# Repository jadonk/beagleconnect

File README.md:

# BeagleConnect
The purpose of BeagleConnect is to eliminate the need to write software to connect to a massive library of [sensors](https://en.wikipedia.org/wiki/Sensor), [actuators](https://en.wikipedia.org/wiki/Actuator) and [indicators](https://en.wikipedia.org/wiki/Indicator_(distance_amplifying_instrument)). These are the tools used to automate things in [mechatronics](https://en.wikipedia.org/wiki/Mechatronics) and [IoT](https://en.wikipedia.org/wiki/Internet_of_things).

BeagleConnect solves:
* The need to write software to add a large set of diverse devices to your system,
* The need to maintain the software with security updates,
* The need to rapidly prototype using off-the-shelf software and hardware without wiring,
* The need to connect to devices using long-range, low-power wireless, and
* The need to produce high-volume custom hardware cost-optimized for your requirements.

The minimally viable BeagleConnect development release:
* Supports at least 100 mikroBUS-based Click boards from Mikroelectronika,
* Works with BLE-enabled Linux computers at 2.4GHz,
* Works on long-range sub-GHz at 500m with data rates of 1kbps, and
* Comprises of low-cost BeagleBoard.org Linux SBC, a BeagleConnect gateway, and at least 10 BeagleConnect device nodes each supporting 2 add-on devices.

A wireless BeagleConnect board for adding a new device node is targeted to cost under US$10.

Future releases will be collaborated with the community, evolve dynamically, and contain additional functionality. The goal is to support over 500 add-on devices within the first year after the development release.

_Aside_: The term BeagleConnect refers to a particular board as well as a family of boards, a collection of Linux kernel drivers, microcontroller firmware, communication protocol, and system-level integration to automation software tools. More specific terms will be applied in the architecture details. The term is meant to represent the experience to be introduced to users through the initial BeagleConnect board.

## BeagleConnect wireless board prototype rev B

# What is new?
BeagleConnect solves IoT in a different and better way than any previous solution.

## The device interface software is already done
BeagleConnect uses the collaboratively developed Linux kernel to contain the intelligence required to speak to these devices (sensors, actuators, and indicators), rather than relying on writing code on a microcontroller specific to these devices. Some existing solutions rely on large libraries of microcontroller code, but the integration of communications, maintenance of the library with a limited set of developer resources and other constraints to be explained later make those other solutions less suitable for rapid prototyping than BeagleConnect.

Linux presents these devices abstractly in ways that are self-descriptive. Add an accelerometer to the system and you are automatically fed a stream of force values in standard units. Add a temperature sensor and you get it back in standard units again. Same for sensing magnetism, proximity, color, light, frequency, orientation, or multitudes of other inputs. Indicators, such as LEDs and displays, are similarly abstracted with a few other kernel subsystems and more advanced actuators with and without feedback control are in the process of being developed and standardized. In places where proper Linux kernel drivers exist, no new specialized code needs to be created for the devices.

*Bottom line*: For hundreds of devices, users won't have to write a single line of code to add them their systems. The automation code they do write can be extremely simple, done with graphical tools or in any language they want. Maintenance of the code is centralized in a small reusable set of microcontroller firmware and the Linux kernel, which is highly peer reviewed under a [highly-regarded governance model](https://wiki.p2pfoundation.net/Linux_-_Governance).

## On-going maintenance
Because there isn't code specific to any given network-of-devices configuration, we can all leverage the same software code base. This means that when someone fixes an issue in either BeagleConnect firmware or the Linux kernel, you benefit from the fixes. The source for BeagleConnect firmware is also submitted to the [Zephyr Project](https://www.zephyrproject.org/) upstream, further increasing the user base. Additionally, we will maintain stable branches of the software and provide mechanisms for updating firmware on BeagleConnect hardware. With a single, relatively small firmware load, the potential for bugs is kept low. With large user base, the potential for discovering and resolving bugs is high.

## Rapid prototyping without wiring
BeagleConnect utilizes the [mikroBUS standard](https://elinux.org/Mikrobus). The mikroBUS standard interface is flexible enough for almost any typical sensor or indicator with hundreds of devices available.

## Long-range, low-power wireless
BeagleConnect wireless hardware is built around a [TI CC1352](http://www.ti.com/product/CC1352R) with TODO benefits.

## Full customization possible
BeagleConnect utilizes [open source hardware](https://www.oshwa.org/definition/) and [open source software](https://en.wikipedia.org/wiki/Open-source_software), making it possible to optimize hardware and software implementations and sourcing to meet end-product requirements. BeagleConnect is meant to enable rapid-prototyping and not to necessarily satisfy any particular end-product's requirements, but with full considerations for go-to-market needs.

BeagleConnect is:
* Available for at least 10 years,
* Built with fully open source software with submissions to mainline Linux and Zephyr repositories to aide in support and porting,
* Built with fully open source and non-restrictive hardware design including schematic, bill-of-materials, layout, and manufacturing files (with only the BeagleBoard.org logo removed due to licensing restrictions of our brand),
* Built with parts where at least a compatible part is available from worldwide distributors in any quantity,
* Built with design and manufacturing partners able to help scale derivative designs,
* Based on a security model using public/private keypairs that can be replaced to secure your own network, and
* Fully FCC/CE certified.

# Usage and development

## BeagleConnect user experience

### Enable a Linux host with BeagleConnect

Log into a host system running Linux that is BeagleConnect enabled. Enable a Linux host with BeagleConnect by plugging a BeagleConnect board into it's USB port. You'll also want to have another BeagleConnect board with a sensor, actuator or indicator device on it.

TODO: Currently the host is shown to be a PocketBeagle with a cape, but should likely be a different SBC with a BeagleConnect board connected over USB.

TODO: Currently the device is shown to be a Sensortag, but should likely be shown as a BeagleConnect with a Click Board device on it and a battery.

### Connect host and device

Initiate a connection between the host and devices by pressing the discovery button(s).

### Device data shows up as files

New streams of self-describing data show up on the host system using native device drivers.

## Components
* Host-side: BeagleConnect board connects a CC1352 to a Beagle or other Linux host over USB to serial
   * Provides long-range, low-power wireless communications
* Device-side: BeagleConnect board with a CC1352 is powered by a battery (coin cell or JST connector) or USB connector
   * Provides 2 mikroBUS connectors for connecting any of hundreds of [Click Board](https://bbb.io/click) mikroBUS add-on devices
* Standard firmware on the host-side and target-side CC1352s transport the standard busses
   * Paired with a Linux kernel driver
   * Provides new Linux host controllers for SPI, I2C, UART, PWM, ADC, and GPIO with interrupts
* Two-step provisioning
   * Enter provisioning mode by pressing the button on the host-side BeagleConnect
   * Press the button on any powered device-side BeagleConnect to add it to the network
      * The device interfaces get exposed to the host via Greybus BRIDGED_PHY protocol
      * The I2C bus is probed for a an identifier EEPROM and appropriate device drivers are loaded on the host
      * Unsupported Click Boards connected are exposed via userspace drivers on the host for development

### What's different
* No microcontroller code development is required by users
* Userspace drivers make rapid prototyping really easy
* Kernel drivers makes the support code collaborative parts of the Linux kernel, rather than cut-and-paste

## Development platform
* Linux machine
* 2x [CC1352R Launchpad](http://www.ti.com/tool/launchxl-cc1352r1)
* [Click BoosterPack 2](https://www.mikroe.com/click-booster-pack-2)

# Technical approach

BeagleConnect uses Greybus and updated Click Boards with identifiers to eliminate the need to add manually configure devices added onto the Linux system.

## High-level
* For Linux nerds: Think of BeagleConnect as [6LoWPAN](https://en.wikipedia.org/wiki/6LoWPAN) over [802.15.4](https://en.wikipedia.org/wiki/IEEE_802.15.4)-based [Greybus](https://kernel-recipes.org/en/2015/talks/an-introduction-to-greybus/) (instead of Unipro as used by Project Ara), where every BeagleConnect board shows up as new SPI, I2C, UART, PWM, ADC, and GPIO controllers that can now be probed to load drivers for the sensors or whatever is connected to them. (Proof of concept of Greybus over TCP/IP: https://www.youtube.com/watch?v=7H50pv-4YXw)
* For MCU folks: Think of BeagleConnect as a [Firmata](https://github.com/firmata/protocol)-style firmware load that exposes the interfaces for remote access over a secured wireless network. However, instead of using host software that knows how to speak the Firmata protocol, the Linux kernel speaks the slightly similar Greybus protocol to the MCU and exposes the device generically to users using a Linux kernel driver. Further, the Greybus protocol is spoken over [6LoWPAN](https://en.wikipedia.org/wiki/6LoWPAN) on [802.15.4](https://en.wikipedia.org/wiki/IEEE_802.15.4).

## Software architecture
* 802.15.4 provides the 

## TODO items
* Linux kernel driver
* Provisioning
   * Kconfig and what-not for adding a new BeagleDust to the network
   * Kconfig and what-not for configuring Clicks connected to BeagleDust
* Firmware for host CC13x
* Firmware for device CC13x
* Click Board drivers and device tree formatted metadata for 100 or so Click Boards
* Click Board plug-ins for node-red for the same 100 or so Click Boards
* BeagleDust System Reference Manual and FAQs

## Associated pre-work
* Click Board support for Node-RED can be executed with native connections on PocketBeagle+TechLab and BeagleBone Black with mikroBUS Cape
   * Device tree fragments and driver updates can be provided via https://bbb.io/click
* The Kconfig style provisioning can be implemented for those solutions, which will require a reboot. We need to centralize edits to /boot/uEnv.txt to be programmatic. As I think through this, I don't think BeagleConnect is impacted, because the Greybus-style discovery along with Click EEPROMS will eliminate any need to edit /boot/uEnv.txt.

## User experience concerns
* Make sure no reboots are required
* Plugging BeagleConnect into host should trigger host configuration
* Click EEPROMs should trigger loading whatever drivers are needed and provisioning should load any new drivers
* Userspace (spidev, etc.) drivers should unload cleanly when 2nd phase provisioning is completed

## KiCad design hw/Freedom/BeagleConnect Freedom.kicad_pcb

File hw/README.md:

# BeagleConnect HW

The LeashPCB is a newer chip based version of BeagleConnect Long-range Wireless BLE(2.4GHz)/802.15.4(SubG), started in June of 2019

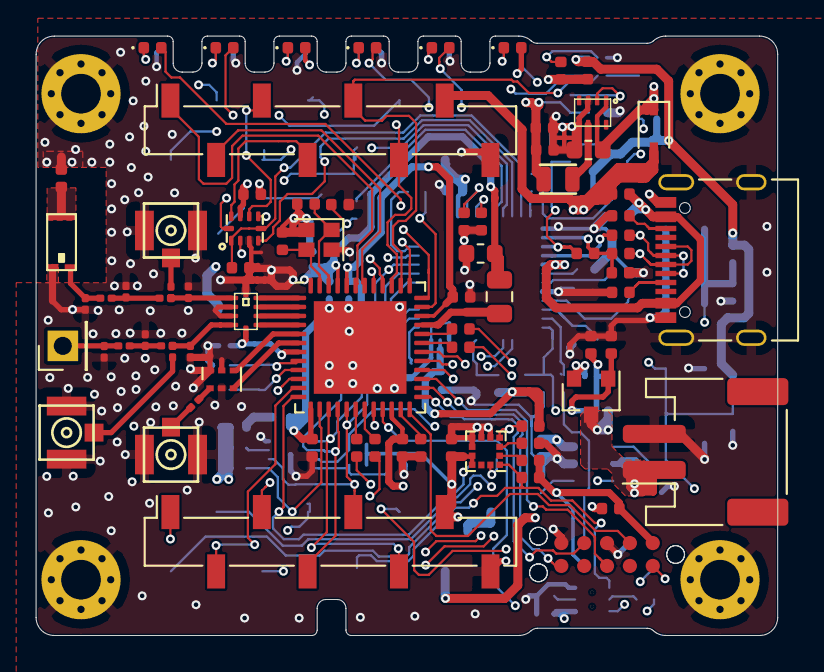
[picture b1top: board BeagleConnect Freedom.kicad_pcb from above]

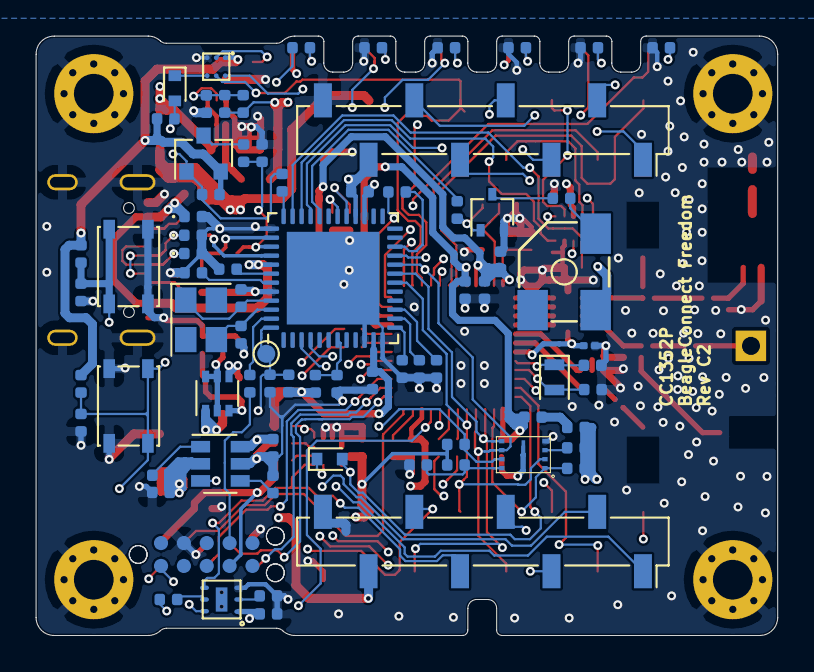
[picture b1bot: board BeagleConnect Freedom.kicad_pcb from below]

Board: 4 copper layers, 41.2 x 33.3 mm, 156 parts (76 on the bottom side), 122 nets.

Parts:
AE1: Antenna_Dipole; RFECA3216060A1T
AE2: Antenna; PinHeader_1x01_P2.54mm_Vertical
B1: 0900PC15A0036E; 0900PC15A0036
B2: 1720BL15B0200E; Anaren_0805_2012Metric-6
BZ1: Buzzer; BUZZER3-5.5X5X2MM
C1, C5, C7, C18, C19, C20, C21, C22, C23, C25, C26, C38, C39, C40, C41, C42: 0.1U; C_0402_1005Metric
C2: 1N; C_0402_1005Metric
C3, C4: 18P; C_0402_1005Metric
C6, C10, C11, C14, C45: 10U; C_0402_1005Metric
C8, C44: 220N; C_0402_1005Metric
C9: 0.47U; C_0402_1005Metric
C12: 10U; C_0603_1608Metric
C13: 100P; C_0402_1005Metric
C15, C16, C48: 12P; C_0402_1005Metric
C17: 1U; C_0402_1005Metric
C24: 22U; C_0603_1608Metric
C27, C28, C35, C36: 100N; C_0201_0603Metric
C29, C30, C31, C32, C33, C43, C46: DNP; C_0201_0603Metric
C34: 12P; C_0201_0603Metric
C37: 1P; C_0402_1005Metric
C47: 7P; C_0402_1005Metric
D2, D3, D4, D5, D6, D7: LED; LED_0402_1005Metric
D8, D10, D11: ESDPSA0402V05; D_0402_1005Metric
D9: BAT54; D_SOD-323
D12, D13: BAT54XV2; D_SOD-523
F1: 500mA; R_0402_1005Metric
H1, H2, H3, H4: Mounting Hole; MountingHole_2.2mm_M2_Pad_Via
J1: Conn_01x02_Male; JST_PH_S2B-PH-SM4-TB_1x02-1MP_P2.00mm_Horizontal
J2, J3: TAG-CONNECT-10; Tag-Connect-10
J4, J5: mikroBUS; MikroBus-SMD
J6, J7, J8: UFL; A-1JB
L1, L3: 120R-1.3A; L_0402_1005Metric
L2: 0.47U; L2X1.6X1MM
L4: 6.8 uH; L_0805_2012Metric
L5, L6: 0; L_0201_0603Metric
P1: USB_C_Receptacle_USB2.0; USB_C_Receptacle_Palconn_UTC16-G
Q1, Q4: CJ2305; SOT-23
Q2: 2N7002PW; SOT-323_SC-70
Q3: BC856S; SOT-363_SC-70-6
R1, R2, R3, R4, R5, R6, R11: 1K; R_0402_1005Metric
R7, R41, R42, R43, R44, R50, R52, R53: 2.21K; R_0402_1005Metric
R8, R9, R12, R35, R46, R47: 100K; R_0402_1005Metric
R10, R15, R23, R24, R25, R26, R27, R28, R29, R36, R37, R38, R39, R40, R45, R48, R49, R51, R54: 0; R_0402_1005Metric
R13: 100R; R_0402_1005Metric
R14, R22: 1M; R_0402_1005Metric
R17, R32: 47K; R_0402_1005Metric
R18, R19: 5.1K; R_0402_1005Metric
R20, R21: 10R0; R_0402_1005Metric
R30: 1.5K; R_0402_1005Metric
R31: 1.2K; R_0402_1005Metric
R34: 453K; R_0402_1005Metric
SW1, SW2: SW_SPST; SW_SPST_PTS810
TP1: TestPoint; TestPoint_Pad_D1.0mm
U1: MSP430F5503; Texas_S-PVQFN-N48_EP5.15x5.15mm
U2: BQ21040; SOT-23-6
U3: TPS62821; TPS62821DLC
U4: CC1352P-LeashPCB; QFN-48-1EP_7x7mm_P0.5mm_EP5.15x5.15mm
U5: TS5A23157; QFN10_0.6_2X1.5X0.5MM
U6: GD25Q16CEIGR; MX25R8035FZUIL0
U7: OPT3001; USON6
U8: HDC2010
U9: LIS2DE12; LGA-12_2x2mm_P0.5mm
Y1: 24MHz; Crystal_SMD_3225-4Pin_3.2x2.5mm
Y2: 32.768KHz; Crystal_SMD_2012-2Pin_2.0x1.2mm
Y3: 48MHz; Crystal_SMD_2016-4Pin_2.0x1.6mm

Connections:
2.4G: D6.2, U4.28
3V3: BZ1.1, C1.1, C6.2, C7.2, C13.1, C14.1, C40.2, C41.2, C42.2, C45.1, D4.2, D7.2, J2.1, J3.4, J4.7, J5.7, L1.2, L2.2, Q1.2, R7.1, R11.1, R17.2, R34.2, R36.2, R41.1, R43.1, R44.1, R45.1, R46.1, R47.1, R50.1, R52.1, R53.1, U1.11, U1.28, U7.1, U8.A1, U9.9, U9.10
5V: C10.2, D9.2, F1.1, J4.10, J5.10, U2.6
900M: D5.2, U4.20
/RF/DCDC_SW: L4.2, U4.33
/RF/RF_2_4GHZ_N: B1.8, U4.2
/RF/RF_2_4GHZ_P: B1.9, U4.1
/RF/RF_SUB_1GHZ_N: B1.6, U4.4
/RF/RF_SUB_1GHZ_P: B1.7, U4.3
/RF/RX_TX: B1.5, C27.2, U4.7
/RF/VDDR: C22.2, C23.2, C24.2, L4.1, U4.45, U4.48
/USB Input/D+: R21.1, R22.1, R30.2, U1.38
/USB Input/D-: R20.1, U1.40
/USB Input/D_N: D10.1, P1.A7, P1.B7, R20.2
/USB Input/D_P: D11.1, P1.A6, P1.B6, R21.2
/USB Input/MSP430_TEST: J3.7, R24.1
/USB Input/MSP_PUR: R13.1, R14.2, R30.1, U1.39
/USB Input/VBUS: D8.1, F1.2, P1.A4, P1.A9, P1.B4, P1.B9, U1.41
/USB Input/XTAL1: C4.2, U1.45, Y1.1
/USB Input/XTAL2: C3.2, U1.46, Y1.3
/USB Input/~MSP430_RST: C2.2, J3.1, R17.1, TP1.1, U1.48
ALT_IN: C11.2, J1.1, Q3.1, Q4.3, R32.2, U2.2
AN_MB1: J4.1, U4.36
AN_MB2: J5.1, U4.37
BUZZER_CTL: R10.2, U1.32
CC1352_RX_MB1_TX: J4.13, U5.9
CC1352_RX_MB2_TX: J5.13, R38.2
CC1352_RX_MSP430_TX: U1.33, U5.2
CC1352_TCK: J2.4, U4.25
CC1352_TDI: J2.8, U4.27
CC1352_TDO: J2.6, U4.26
CC1352_TMS: J2.2, U4.24
CC1352_TX_MB1_RX: J4.14, U5.7
CC1352_TX_MB2_RX: J5.14, R37.2
CC1352_TX_MSP430_RX: U1.34, U5.4
CS_MB1: J4.3, U4.41
CS_MB2: J5.3, U4.40
GND: AE1.2, B1.2, B1.3, B1.10, B2.2, B2.5, B2.6, C1.2, C2.1, C3.1, C4.1, C5.1, C6.1, C7.1, C8.1, C9.1, C10.1, C11.1, C12.2, C14.2, C15.2, C16.2, C17.1, C18.1, C19.1, C20.1, C21.1, C22.1, C23.1, C24.1, C25.1, C26.1, C27.1, C29.1, C30.2, C31.1, C32.2, C37.2, C38.1, C39.1, C40.1, C41.1, C42.1, C43.1, C44.1, C45.2, C46.2, C47.2, C48.2, D8.2, D10.2, D11.2, H1.1, H2.1, H3.1, H4.1, J1.2, J2.3, J2.5, J3.9, J4.8, J4.9, J5.8, J5.9, J6.2, J6.3, J7.2, J7.3, J8.2, J8.3, P1.A1, P1.A12, P1.B1, P1.B12, P1.S1, Q2.2, R1.2, R2.2, R3.2, R4.2, R5.2, R8.1, R9.1, R12.2, R14.1, R18.2, R19.2, R22.2, R26.1, R27.1, R28.1, R29.1, R31.2, R35.1, R42.2, R48.1, R51.2, R54.2, SW1.2, SW2.2, U1.10, U1.12, U1.27, U1.37, U1.44, U1.49, U2.5, U3.3, U3.5, U4.49, U5.3, U6.4, U6.9, U7.3, U8.C1, U9.5, U9.6, U9.7, U9.8, Y3.2, Y3.4
INT_HDC2010: D12.1, U8.C2
INT_LIS2DE12_1: D13.1, U9.12
INT_MB1: J4.15, U4.42
INT_MB2: J5.15, U4.30
INT_SENSOR: D12.2, D13.2, R7.2, R49.1, U4.12
LED1: D3.2, U1.3
LED2: D2.2, U1.4
MB1_CTRL: R42.1, U1.35, U5.1, U5.5
MISO: J4.5, J5.5, U1.18, U4.17, U6.2
MOSI: J4.6, J5.6, U1.19, U4.15, U6.5
unnamed: AE1.1, C31.2, L5.1
unnamed: AE1.3, C37.1
unnamed: AE2.1, C32.1, L6.1
unnamed: B1.1, C33.1, C34.1, C43.2
unnamed: B1.4, C28.1, C36.1, C46.1
unnamed: B2.1, C35.1
unnamed: B2.3, U4.6
unnamed: B2.4, U4.5
unnamed: BZ1.2, R15.1
unnamed: C5.2, L1.1, U1.7
unnamed: C8.2, U1.43
unnamed: C9.2, U1.13
unnamed: C13.2, R34.1, R35.2, U3.2
unnamed: C15.1, U4.8, Y2.1
unnamed: C16.1, U4.9, Y2.2
unnamed: C17.2, U4.23
unnamed: C26.2, R45.2, U6.8
unnamed: C28.2, J7.1
unnamed: C29.2, C34.2, L5.2
unnamed: C30.1, C36.2, L6.2
unnamed: C33.2, J6.1
unnamed: C35.2, J8.1
unnamed: C44.2, U1.42
unnamed: C47.1, U4.46, Y3.1
unnamed: C48.1, U4.47, Y3.3
unnamed: D2.1, R1.1
unnamed: D3.1, R2.1
unnamed: D4.1, R3.1
unnamed: D5.1, R4.1
unnamed: D6.1, R5.1
unnamed: D7.1, R6.1
unnamed: L2.1, U3.6
unnamed: P1.A5, R19.1
unnamed: P1.B5, R18.1
unnamed: Q1.3, R13.2
unnamed: Q2.1, R10.1, R12.1
unnamed: Q2.3, R15.2
unnamed: Q3.2, Q3.5, Q3.6, R8.2
unnamed: Q3.3, Q4.1, R9.2
unnamed: R23.2, U1.22
unnamed: R24.2, U1.47
unnamed: R25.2, U1.36
unnamed: R26.2, U1.14
unnamed: R27.2, U1.15
unnamed: R28.2, U1.29
unnamed: R29.2, U1.30
unnamed: R31.1, U2.4
unnamed: R32.1, U2.1
unnamed: R37.1, U4.31
unnamed: R38.1, U4.32
unnamed: R39.1, U4.18
unnamed: R39.2, U5.10
unnamed: R40.1, U4.19
unnamed: R40.2, U5.6
unnamed: R43.2, U6.3
unnamed: R48.2, U7.2
unnamed: R49.2, U7.5
unnamed: R51.1, U8.B1
unnamed: R53.2, U9.2
unnamed: R54.1, U9.3
PWM_MB1: J4.16, U4.43
PWM_MB2: J5.16, U4.29
RESET_N: C38.2, J2.10, R23.1, R41.2, R46.2, SW1.1, U4.35, U6.7
RST_MB1: J4.2, U4.11
RST_MB2: J5.2, U4.10
SCK: J4.4, J5.4, U1.20, U4.16, U6.6
SCL: J4.12, J5.12, R50.2, U4.38, U7.4, U8.B2, U9.1
SDA: J4.11, J5.11, R52.2, U4.39, U7.6, U8.A2, U9.4
USER_BOOT: C39.2, Q1.1, R11.2, R25.1, R47.2, SW2.1, U4.21
VDD: L3.2, R36.1
VDDS: C18.2, C19.2, C20.2, C21.2, C25.2, L3.1, U4.13, U4.22, U4.34, U4.44, U5.8
V_ALT: C12.1, D9.1, Q3.4, Q4.2, U3.1, U3.7
~CHG: R6.2, U2.3
~FLASH_CS: R44.2, U1.21, U4.14, U6.1

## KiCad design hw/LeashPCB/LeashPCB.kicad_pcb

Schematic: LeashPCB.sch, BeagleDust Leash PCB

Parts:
H101, H102, H103, H104: Mounting Hole; MountingHole_2.2mm_M2_Pad_Via; MPN1 N/A

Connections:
GND: H101.1, H102.1, H103.1, H104.1; also elsewhere on the board

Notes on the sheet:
Power Conversion
Alt Power Input
RF and Processor
Programming
Indicators
MikroBus Headers
Estimated BOM cost: $0.60
Estimated BOM cost: $1.27
Estimated BOM cost: $0.03
Estimated BOM cost: $0.15
Estimated BOM cost: $0.00
USB Input (Power/serial)
Estimated BOM cost: $1.00 ($0.02 without serial to usb)
Estimated BOM cost: $0.05
User I/O

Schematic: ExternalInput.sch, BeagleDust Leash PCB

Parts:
D301: BAT54; D_SOD-123; MPN1 BAT54GWJ
J301: Conn_01x02_Male; JST_PH_S2B-PH-SM4-TB_1x02-1MP_P2.00mm_Horizontal; MPN1 S2B-PH-SM4-TB(LF)(SN)

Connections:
3V3: J301.1; also elsewhere on the board

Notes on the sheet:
No pop if using the switch/jumper method

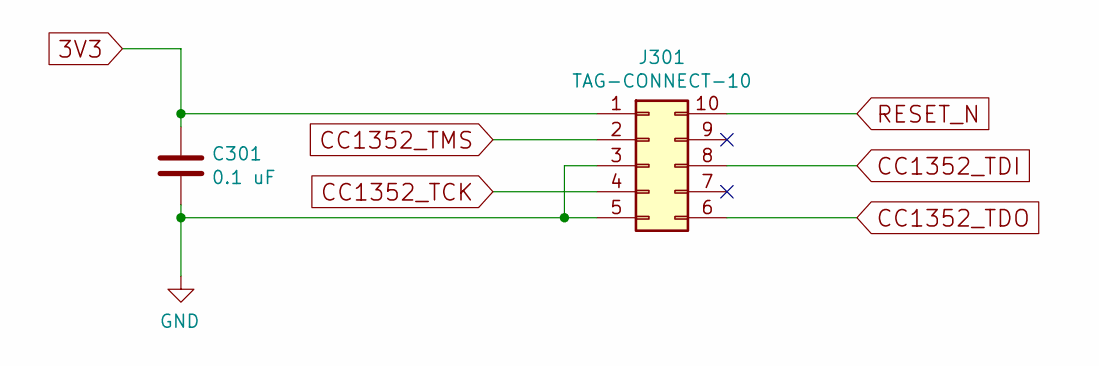
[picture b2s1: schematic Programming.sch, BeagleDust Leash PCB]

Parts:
C301: 0.1 uF; C_0402_1005Metric; MPN1 CL05A104MP5NNNC
J301: TAG-CONNECT-10; Tag-Connect-10; MPN1 N/A

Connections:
3V3: C301.1, J301.1; also elsewhere on the board
CC1352_TCK: J301.4; also elsewhere on the board
CC1352_TDI: J301.8; also elsewhere on the board
CC1352_TDO: J301.6; also elsewhere on the board
GND: C301.2, J301.3, J301.5; also elsewhere on the board
RESET_N: J301.10; also elsewhere on the board

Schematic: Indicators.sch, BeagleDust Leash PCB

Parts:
D401, D402, D403, D404, D405: LED; LED_0402_1005Metric; MPN1 SML-D12U1WT86
R401, R402, R403, R404, R405: 1K; R_0402_1005Metric; MPN1 RC0402JR-071KL

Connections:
2.4G: D405.2; also elsewhere on the board
3V3: D403.2; also elsewhere on the board
900M: D404.2; also elsewhere on the board
GND: R401.2, R402.2, R403.2, R404.2, R405.2; also elsewhere on the board
LED1: D402.2; also elsewhere on the board
LED2: D401.2; also elsewhere on the board
unnamed: D401.1, R401.1
unnamed: D402.1, R402.1
unnamed: D403.1, R403.1
unnamed: D404.1, R404.1
unnamed: D405.1, R405.1

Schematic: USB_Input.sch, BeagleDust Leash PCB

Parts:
C501, C503: 0.1 uF; C_0402_1005Metric; MPN1 CL05A104MP5NNNC
C502, C508, C509: 10U; C_0402_1005Metric; MPN1 CL05A104MP5NNNC
C504: 220N; C_0402_1005Metric; MPN1 0402ZD224KAT2A
C505: 0.47U; C_0402_1005Metric; MPN1 CL05A474KP5NNNC
C506, C507: 18P; C_0402_1005Metric; MPN1 C0402C180J5GAC7867
D501: BAT54; D_SOD-123; MPN1 BAT54GWJ
D502: TPD2E001; SOT-23-5; MPN1 TPD2E001DRLR
F501: Polyfuse; R_0603_1608Metric; MPN1 PTC RESET FUSE 6V 350MA 0603
J501: TAG-CONNECT-10; Tag-Connect-10; MPN1 N/A
L501: 6.8 uH; L_0603_1608Metric; MPN1 BLM18HE152SN1D
P501: USB_C_Plug_USB2.0; USB_C_Receptacle_Palconn_UTC16-G; MPN1 ST-USB-3316
R501, R502: 5.1K; R_0402_1005Metric; MPN1 RC0402JR-075K1L
R503, R504: 10R0; R_0402_1005Metric; MPN1 RC0402JR-0710RL
R505: 1M; R_0402_1005Metric; MPN1 RC0402JR-071ML
R506: 1K; R_0402_1005Metric; MPN1 RC0402JR-071KL
R507, R509, R510, R511: 0; R_0402_1005Metric; MPN1 RMCF0402ZT0R00
R508: 1.5K; R_0402_1005Metric; MPN1 RC0402JR-071K5L
U501: MSP430F5500; Texas_S-PVQFN-N48_EP5.15x5.15mm; MPN1 MSP430F5500IRGZR
U502: BQ21040; SOT-23-6; MPN1 BQ21040DBVR
Y501: 24MHz; Crystal_SMD_3225-4Pin_3.2x2.5mm; MPN1 ABM8-24.000MHZ-B2-T

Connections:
3V3: C502.2, C503.2, J501.1, L501.2, U501.11, U501.28; also elsewhere on the board
5V: C508.2, D501.2, F501.1, U502.6; also elsewhere on the board
/USB Input/D+: R504.1, R505.1, R508.2, U501.38
/USB Input/D-: R503.1, U501.40
/USB Input/D_N: D502.5, P501.A7, R503.2
/USB Input/D_P: D502.3, P501.A6, R504.2
/USB Input/MSP430_RST_N: J501.10, U501.48
/USB Input/MSP430_TCK: J501.4, U501.26
/USB Input/MSP430_TDI: J501.8, U501.24
/USB Input/MSP430_TDO: J501.6, U501.23
/USB Input/MSP430_TMS: J501.2, U501.25
/USB Input/MSP_PUR: R508.1, U501.39
/USB Input/VBUS: D502.1, F501.2, P501.A4, P501.A9, P501.B4, P501.B9, U501.41, U501.42
/USB Input/XTAL1: C507.2, U501.45, Y501.1
/USB Input/XTAL2: C506.2, U501.46, Y501.3
ALT_IN: C509.2, U502.2; also elsewhere on the board
CC1352_RX_MSP430_TX: U501.15; also elsewhere on the board
CC1352_TX_MSP430_RX: U501.16; also elsewhere on the board
GND: C501.1, C502.1, C503.1, C504.1, C505.1, C506.1, C507.1, C508.1, C509.1, D502.4, J501.3, J501.5, P501.A1, P501.A12, P501.B1, P501.B12, P501.S1, R501.2, R502.2, R505.2, R506.2, R509.1, R510.1, U501.10, U501.12, U501.27, U501.37, U501.44, U501.49, U502.5, Y501.2, Y501.4; also elsewhere on the board
MISO: U501.18; also elsewhere on the board
MOSI: U501.19; also elsewhere on the board
unnamed: C501.2, L501.1, U501.7
unnamed: C504.2, U501.43
unnamed: C505.2, U501.13
unnamed: P501.A5, R502.1
unnamed: P501.B5, R501.1
unnamed: R506.1, U502.4
unnamed: R507.2, U501.17
unnamed: R509.2, U501.29
unnamed: R510.2, U501.30
unnamed: R511.2, U501.22
RESET_N: R511.1; also elsewhere on the board
SCK: U501.20; also elsewhere on the board
USER1: R507.1; also elsewhere on the board
V_ALT: D501.1; also elsewhere on the board
~CHG: U502.3; also elsewhere on the board
~FLASH_CS: U501.21; also elsewhere on the board

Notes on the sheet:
USB C input
Decoupling cap shared with other prog header

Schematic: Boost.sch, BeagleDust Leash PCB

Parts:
C601: 1 uF; C_0402_1005Metric; MPN1 CL05A104MP5NNNC
C602: 100 pF; C_0402_1005Metric; MPN1 CC0402JRNPO9BN101
C603: 10 uF; C_0603_1608Metric; MPN1 CL10A106MQ8NNNC
L601: 0.47U; L_0806_2012Metric; MPN1 ASMPM-0806-R47M-T
R601, R603: 100K; R_0402_1005Metric; MPN1 RC0402JR-07100KL
R602: 453K; R_0402_1005Metric; MPN1 RMCF0402FT453K
R604: 0; R_0402_1005Metric; MPN1 RMCF0402ZT0R00
U601: TPS62821; TPS62821DLC; MPN1 TPS62821DLCR

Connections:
3V3: R604.1; also elsewhere on the board
/Boost Converters/3V3_BUCK_VOUT: C602.1, C603.1, L601.2, R602.2, R604.2
GND: C601.2, C603.2, R603.1, U601.3, U601.5; also elsewhere on the board
unnamed: C602.2, R602.1, R603.2, U601.2
unnamed: L601.1, U601.6
unnamed: R601.1, U601.8
V_ALT: C601.1, R601.2, U601.1, U601.7; also elsewhere on the board

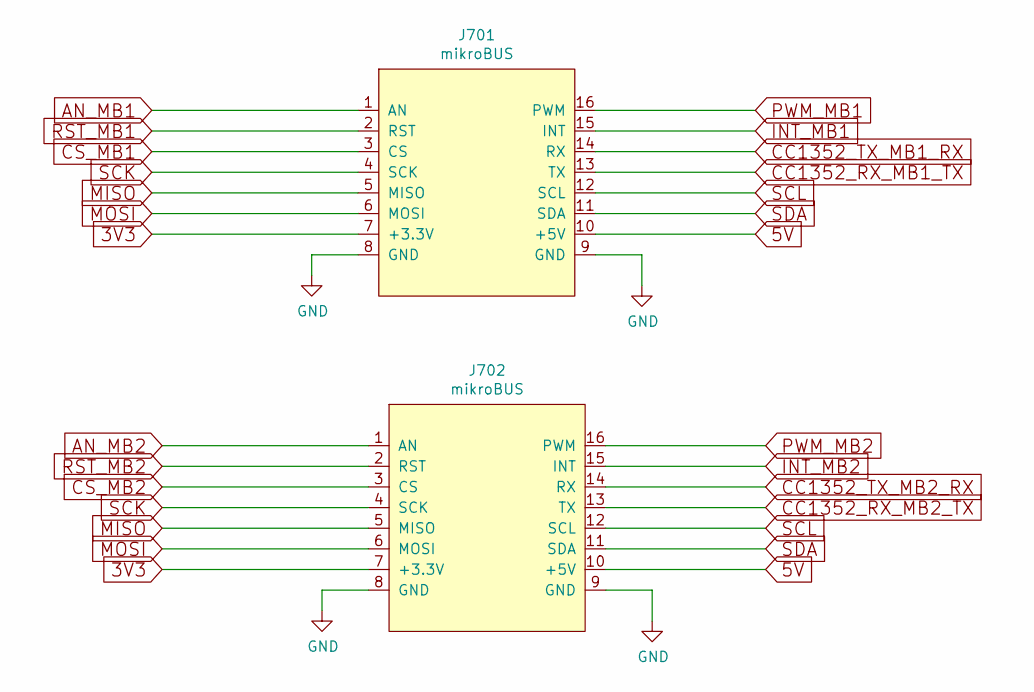
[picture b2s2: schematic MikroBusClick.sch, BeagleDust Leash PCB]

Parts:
J701, J702: mikroBUS; MikroBus-SMD; MPN1 NPTC081KFXC-RC

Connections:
3V3: J701.7 (+3.3V), J702.7 (+3.3V); also elsewhere on the board
5V: J701.10 (+5V), J702.10 (+5V); also elsewhere on the board
AN_MB1: J701.1 (AN); also elsewhere on the board
AN_MB2: J702.1 (AN); also elsewhere on the board
CC1352_RX_MB1_TX: J701.13 (TX); also elsewhere on the board
CC1352_RX_MB2_TX: J702.13 (TX); also elsewhere on the board
CC1352_TX_MB1_RX: J701.14 (RX); also elsewhere on the board
CC1352_TX_MB2_RX: J702.14 (RX); also elsewhere on the board
CS_MB1: J701.3 (CS); also elsewhere on the board
CS_MB2: J702.3 (CS); also elsewhere on the board
GND: J701.8 (GND), J701.9 (GND), J702.8 (GND), J702.9 (GND); also elsewhere on the board
INT_MB1: J701.15 (INT); also elsewhere on the board
INT_MB2: J702.15 (INT); also elsewhere on the board
MISO: J701.5 (MISO), J702.5 (MISO); also elsewhere on the board
MOSI: J701.6 (MOSI), J702.6 (MOSI); also elsewhere on the board
PWM_MB1: J701.16 (PWM); also elsewhere on the board
PWM_MB2: J702.16 (PWM); also elsewhere on the board
RST_MB1: J701.2 (RST); also elsewhere on the board
RST_MB2: J702.2 (RST); also elsewhere on the board
SCK: J701.4 (SCK), J702.4 (SCK); also elsewhere on the board
SCL: J701.12 (SCL), J702.12 (SCL); also elsewhere on the board
SDA: J701.11 (SDA), J702.11 (SDA); also elsewhere on the board

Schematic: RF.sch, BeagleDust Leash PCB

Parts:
AE801: Antenna_Dipole; RFECA3216060A1T; MPN1 RFECA3216060A1T
AE802: Antenna; PinHeader_1x01_P2.54mm_Vertical; MPN1 N/A
B801: 0900PC15A0036E; 0900PC15A0036; MPN1 0900PC15A0036E
C801, C802: 12 pF; C_0402_1005Metric; MPN1 CL05C120JB5NNNC
C803: 1 uF; C_0402_1005Metric; MPN1 CL05A104MP5NNNC
C804, C805, C806, C807, C808, C809, C811: 0.1 uF; C_0402_1005Metric; MPN1 CL05A104MP5NNNC
C810: 22 uF; C_0603_1608Metric; MPN1 GRM188R61A226ME15D
C812, C813: 100P; C_0402_1005Metric; MPN1 GRM1555C1H101JA01J
C814, C816, C818, C819, C820, C821, C822: 1 pF; C_0402_1005Metric; MPN1 GRM1555C1H1R0CA01D
C815: 2.7 pF; C_0402_1005Metric; MPN1 CC0402CRNPO9BN2R7
C817: 5.6 pF; C_0402_1005Metric; MPN1 CC0402DRNPO9BN5R6
F801: Polyfuse; R_0603_1608Metric; MPN1 RC0603JR-070RL
J801, J802: UFL; A-1JB; MPN1 A-1JB
L801: 6.8 uH; L_0603_1608Metric; MPN1 BLM18HE152SN1D
L802: 6.8 uH; L_0805_2012Metric; MPN1 742792097
L803: 0; L_0402_1005Metric; MPN1 RMCF0402ZT0R00
L804: 0; R_0402_1005Metric; MPN1 RMCF0402ZT0R00
R802, R803, R804, R805, R811: 0; R_0402_1005Metric; MPN1 RMCF0402ZT0R00
R807, R809, R810: 2.21K; R_0402_1005Metric; MPN1 ERJ-2RKF2211X
U801: CC1352R; QFN-48-1EP_7x7mm_P0.5mm_EP5.15x5.15mm; MPN1 CC1352P1F3RGZT
U802: MX25R8035FZUIL0; MPN1 MX25R8035FZUIL0
Y801: Crystal; Crystal_SMD_2012-2Pin_2.0x1.2mm; MPN1 ECS-.327-7-12-C-TR
Y802: Crystal_GND2; Crystal_SMD_2016-4Pin_2.0x1.6mm; MPN1 NX2016SA-48M-EXS00A-CS05517

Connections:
2.4G: U801.9 (DIO_4); also elsewhere on the board
3V3: F801.2; also elsewhere on the board
900M: U801.8 (DIO_3); also elsewhere on the board
/RF/DCDC_SW: L802.2, U801.33 (DCDC_SW)
/RF/RF_2_4GHZ_N: B801.8, U801.2 (RF_N_2_4GHZ)
/RF/RF_2_4GHZ_P: B801.9, U801.1 (RF_P_2_4GHZ)
/RF/RF_SUB_1GHZ_N: B801.6, U801.4 (RF_N_SUB_1GHZ)
/RF/RF_SUB_1GHZ_P: B801.7, U801.3 (RF_P_SUB_1GHZ)
/RF/RX_TX: B801.5, C812.2, U801.5 (RX_TX)
/RF/VDDR: C808.2, C809.2, C810.2, L802.1, U801.45 (VDDR), U801.48 (VDDR_RF)
AN_MB1: U801.36 (DIO_23); also elsewhere on the board
AN_MB2: U801.37 (DIO_24); also elsewhere on the board
CC1352_RX_MB1_TX: R805.1, U801.40 (DIO_27); also elsewhere on the board
CC1352_RX_MB2_TX: R803.2; also elsewhere on the board
CC1352_RX_MSP430_TX: R805.2; also elsewhere on the board
CC1352_TCK: U801.25 (JTAG_TCKC); also elsewhere on the board
CC1352_TDI: U801.27 (DIO_17/JTAG_TDI); also elsewhere on the board
CC1352_TDO: U801.26 (DIO_16/JTAG_TDO); also elsewhere on the board
CC1352_TX_MB1_RX: R804.1, U801.41 (DIO_28); also elsewhere on the board
CC1352_TX_MB2_RX: R802.2; also elsewhere on the board
CC1352_TX_MSP430_RX: R804.2; also elsewhere on the board
CS_MB1: U801.19 (DIO_13); also elsewhere on the board
CS_MB2: U801.18 (DIO_12); also elsewhere on the board
GND: AE801.2, B801.2, B801.3, B801.10, C801.2, C802.2, C803.1, C804.1, C805.1, C806.1, C807.1, C808.1, C809.1, C810.1, C811.1, C812.1, C814.1, C815.2, C816.1, C817.2, C822.2, J801.2, J801.3, J801.4, J802.2, J802.3, J802.4, U801.49 (GND/EP), U802.4, U802.9, Y802.2, Y802.4; also elsewhere on the board
INT_MB1: U801.42 (DIO_29); also elsewhere on the board
INT_MB2: U801.30 (DIO_20); also elsewhere on the board
INT_SENSOR: U801.12 (DIO_7); also elsewhere on the board
LED1: U801.21 (DIO_15); also elsewhere on the board
LED2: U801.28 (DIO_18); also elsewhere on the board
MISO: U801.17 (DIO_11), U802.2; also elsewhere on the board
MOSI: U801.15 (DIO_9), U802.5; also elsewhere on the board
unnamed: AE801.1, C819.2
unnamed: AE801.3, C822.1
unnamed: AE802.1, C820.2
unnamed: B801.1, C814.2, L803.2
unnamed: B801.4, C813.1
unnamed: C801.1, U801.6 (X32K_Q1), Y801.1
unnamed: C802.1, U801.7, U801.~ (X32K_Q2), Y801.2
unnamed: C803.2, U801.23 (DCOUPL)
unnamed: C811.2, R811.2, U802.8
unnamed: C813.2, C815.1, L804.2
unnamed: C816.2, C818.1, C819.1, L803.1
unnamed: C817.1, C820.1, C821.1, L804.1
unnamed: C818.2, J801.1
unnamed: C821.2, J802.1
unnamed: R802.1, U801.31 (DIO_21)
unnamed: R803.1, U801.32 (DIO_22)
unnamed: R809.2, U802.3
unnamed: U801.46 (X48M_N), Y802.1
unnamed: U801.47 (X48M_P), Y802.3
PWM_MB1: U801.43 (DIO_30); also elsewhere on the board
PWM_MB2: U801.29 (DIO_19); also elsewhere on the board
RESET_N: R807.2, U801.35 (RESET_N), U802.7; also elsewhere on the board
RST_MB1: U801.11 (DIO_6); also elsewhere on the board
RST_MB2: U801.10 (DIO_5); also elsewhere on the board
SCK: U801.16 (DIO_10), U802.6; also elsewhere on the board
SCL: U801.38 (DIO_25); also elsewhere on the board
SDA: U801.39 (DIO_26); also elsewhere on the board
USER1: U801.20 (DIO_14); also elsewhere on the board
VDD: F801.1, L801.2
VDDS: C804.2, C805.2, C806.2, C807.2, L801.1, R807.1, R809.1, R810.1, R811.1, U801.13 (VDDS2), U801.22 (VDDS3), U801.34 (VDDS_DCDC), U801.44 (VDDS); also elsewhere on the board
~FLASH_CS: R810.2, U801.14 (DIO_8), U802.1; also elsewhere on the board

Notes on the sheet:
Optional sense resistor for power measurement

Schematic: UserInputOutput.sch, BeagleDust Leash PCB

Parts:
C906, C907: 0.1 uF; C_0402_1005Metric; MPN1 CL05A104MP5NNNC
R901, R902: 100K; R_0402_1005Metric; MPN1 RC0402JR-07100KL
SW901, SW902: SW_SPST; SW_SPST_PTS810; MPN1 EVQ-P7A01P

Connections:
GND: SW901.2, SW902.2; also elsewhere on the board
unnamed: C906.1, C907.1
RESET_N: C906.2, R901.2, SW901.1; also elsewhere on the board
USER1: C907.2, R902.2, SW902.1; also elsewhere on the board
VDDS: R901.1, R902.1; also elsewhere on the board

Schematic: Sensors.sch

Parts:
C1001, C1002: 0.1 uF; C_0402_1005Metric; MPN1 CL05A104MP5NNNC
R1001, R1002: 2.21K; R_0402_1005Metric; MPN1 ERJ-2RKF2211X
R1003, R1004, R1005, R1006, R1007, R1008: 0; R_0402_1005Metric; MPN1 RMCF0402ZT0R00
U1001: HDC2010; MPN1 HDC2010YPAR
U1002: SN74AUP2G32; X2SON-8_1.4x1mm_P0.35mm; MPN1 SN74AUP2G32DQER
U1003: OPT3001; USON6; MPN1 OPT3001DNPR
U1004: LIS2DE12; LGA-12_2x2mm_P0.5mm; MPN1 LIS2DE12TR

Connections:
GND: C1001.1, C1002.1, R1004.2, R1005.2, R1008.1, U1001.C1, U1002.4, U1003.3, U1004.5, U1004.6, U1004.7, U1004.8; also elsewhere on the board
INT_HDC2010: U1001.C2, U1002.1
INT_LIS2DE12_2: R1006.1, U1004.11
INT_OPT3001: R1007.1, U1003.5
INT_SENSOR: U1002.3; also elsewhere on the board
unnamed: R1003.1, U1002.7
unnamed: R1003.2, U1002.6
unnamed: R1004.1, U1001.B1
unnamed: R1005.1, U1004.3
unnamed: R1006.2, R1007.2, U1002.2
unnamed: R1008.2, U1003.2
SCL: R1001.2, U1001.B2, U1003.4, U1004.1; also elsewhere on the board
SDA: R1002.2, U1001.A2, U1003.6, U1004.4; also elsewhere on the board
VDDS: C1001.2, C1002.2, R1001.1, R1002.1, U1001.A1, U1002.8, U1003.1, U1004.9, U1004.10; also elsewhere on the board

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
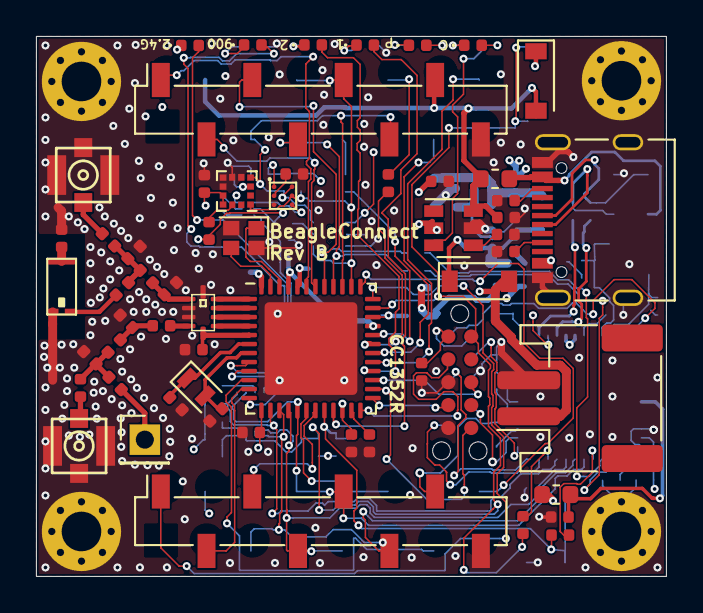
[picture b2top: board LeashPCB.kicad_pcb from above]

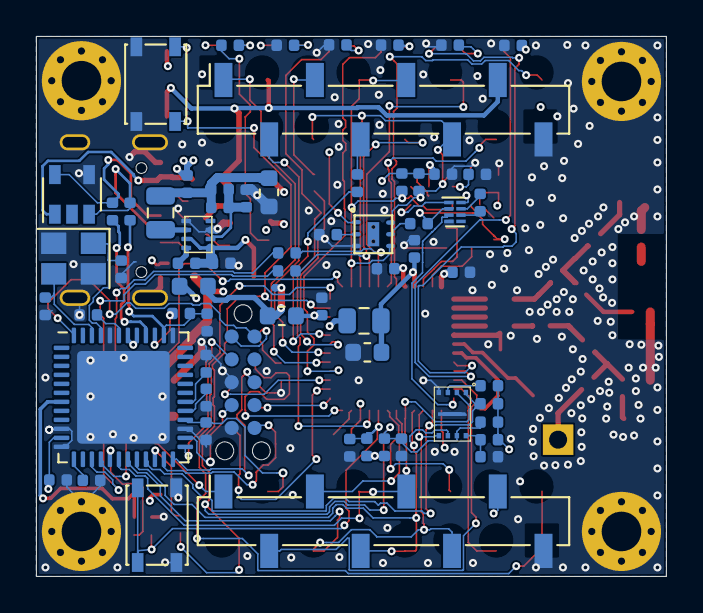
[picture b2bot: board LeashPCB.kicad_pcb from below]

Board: 4 copper layers, 35.0 x 30.0 mm, 124 parts (64 on the bottom side), 109 nets.

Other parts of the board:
C901, C902: 0.1 uF; C_0402_1005Metric
D201: BAT54; D_SOD-123
D406: LED; LED_0402_1005Metric
J201: Conn_01x02_Male; JST_PH_S2B-PH-SM4-TB_1x02-1MP_P2.00mm_Horizontal
R406: 1K; R_0402_1005Metric

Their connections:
3V3: D406.2; also elsewhere on the board
ALT_IN: D201.2, J201.1; also elsewhere on the board
GND: C901.1, C902.1, J201.2; also elsewhere on the board
unnamed: D406.1, R406.1
RESET_N: C901.2; also elsewhere on the board
USER1: C902.2; also elsewhere on the board
V_ALT: D201.1; also elsewhere on the board
~CHG: R406.2; also elsewhere on the board

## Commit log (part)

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2020-10-15 SW: buildroot: try to get greybus/gb-netlink again
2020-10-15 CI: work without false artifacts
2020-10-15 Revert "CI: buildroot: try to fix path"
    This reverts commit bc7215f468d8e56b353f83a0a2b66bf822c7b918.
2020-10-16 SW: buildroot: gbridge: trying to fix pthreads issue
2020-10-16 SW: buildroot: add strace
2020-10-17 CI: buildroot: try different pattern match
2020-10-17 SW: gbridge: remove kernel version check
2020-10-18 SW: buildroot: WIP atusb lowpan connection
    ```
    usb 1-1: ATUSB: AT86RF231 version 2
    usb 1-1: Firmware: major: 0, minor: 3, hardware type: ATUSB (2)
    usb 1-1: Firmware: build #132 Mo 28. Nov 16:20:35 CET 2016
    usb 1-1: Read permanent extended address 10:e2:d5:ff:ff:00:02:d1 from device
    usbcore: registered new interface driver atusb
2020-10-18 SW: buildroot: linux: add CONFIG_BRIDGE
2020-10-18 SW: buildroot: linux: build-in greybus and atusb
2020-10-18 SW: buildroot/gbridge: try to debug
    ```
    netlink: Initializing the controller
    TCP/IP: Initializing the controller
    TCP/IP: Creating the event loop thread
    A driver has already been registered for cport id 0
    Driver is at 0x500010008
2020-10-19 SW: gbridge: cleanup
2020-10-19 SW: buildroot: add dropbear sshd
2020-10-20 SW: buildroot: add mikrobus.config fragment
2020-10-20 SW: buildroot: add root password
2020-10-20 SW: buildroot: linux: updated 6lowpan/driver config
2020-10-22 SW: buildroot: add run script
2020-10-26 SW: linux: add hm3301 makefile
2020-10-26 SW: buildroot: enable HM3301 driver
2020-10-28 README: formatting
2020-10-29 README: Rename to Freedom
2020-10-29 CI: zephyr: add potential dependencies
2020-10-29 CI: add usb_wpan_temp
2020-10-29 CI: buildroot: try to speed up and reduce download size
2020-10-29 CI: zephyr: cache sdk
2020-10-29 SW: buildroot: add wpanusb
2020-10-29 CI: zepher: enable CCACHE
2020-10-29 CI: update ccache cache
2020-10-29 CI: try to fix timestamp
2020-10-30 CI: more build speedups
    * buildroot: disable host tool upload for now
    * zephyr: add cache for pip
2020-10-30 SW: zephyr: merge raw support
2020-10-30 CI: zephyr: recurse submodules
2020-10-30 CI: buildroot: hack in find newer downloads
2020-11-02 CI/README: WIP
2020-11-02 HW: rename Leash to Freedom
2020-11-02 HW: Freedom: reproduce schematic PDF
2020-11-03 SW: zephyr: update subghz config
2020-11-03 HW: Freedom: rev C2 (1103)
    * Rotate mikroBUS to avoid buttons https://github.com/jadonk/beagleconnect/issues/29
    * Released to prototype
2020-11-04 CI/README/wpanusb_bc: debug attempts
    * Use of latest zephyr
    * Transmit threshold increase
2020-11-05 CI: zephyr: subg conf path
2020-11-05 CI: zephyr: try to fix string literal
2020-11-06 SW: greybus: per Chris Friedt
2020-11-09 SW: net-up.sh: move back to channel 1
2020-11-15 SW/README: bad attempt to add scripts
2020-11-18 SW: bcf_sensortest: Import from cfriedt
2020-11-19 HW: restore Leash rev C temporarily
    This is probably adding a lot of wasteful bits, but we are doing a lot of compares between
    this rev C and the Freedom rev C2.
2020-11-19 SW: bcf_sensortest: switch UART
    Still some fixes needed
    ```
    jkridner@tupper:~/workspace/beagleconnect/sw/zephyrproject/bcf_sensortest$ tio /dev/ttyACM1
    [tio 09:41:22] tio v1.29
    [tio 09:41:22] Press ctrl-t q to quit
    [tio 09:41:22] Connected
2020-11-19 SW: zephyr beagleconnect_freedom move console UART
2020-11-20 CI: zephyr: use beagleconnect_freedom
2020-11-20 CI: zephyr: add bcf_sensortest artifact
2020-12-06 SW: bcf_sensortest: send data on regular interval
2020-12-06 CI: try to fix path
2020-12-06 CI: try resetting ccache
2020-12-06 CI: remove unused Jekyll
2020-12-08 SW: buildroot: add Ubuntu dependencies
2020-12-10 SW: bcf_sensortest: flash SubG
2020-12-10 SW: zephyr: update cmake and drive strength
2020-12-12 SW: bcf_sensortest: remove strncat
2020-12-14 SW: zephyr: greybus-for-zephyr as a module
2020-12-14 SW: more notes in setup.sh
2020-12-17 SW: zephyr: reduce size and add launchpad
    * Use a much smaller-in-scope west.yml, loading less modules
    * Add CC1352R1 LaunchpadXL support to `sensortest`
    * Simplify the device selection in `sensortest`
    * Add dummy nodes to the device tree to avoid errors, even if the device
    isn't there
2020-12-17 SW: sensortest: still unclear on names vs labels
2020-12-18 "SW: sensortest: get launchpad working with BME680"
2021-01-13 sw: linux: add mikrobus driver update patches
    mikrobus driver works within buildroot but the click
    device drivers are not being probed correctly:
    in host /opt/gbridge.sh a hack for continously blinking the
    led on the SensorTag/Launchpad is added(this background
    transaction happening continously prevents some of the greybus
    pm suspend events happening, which might have been the cause
2021-01-15 Update 0007-mikrobus-mikrobus-over-greybus.patch
    I'll need to track down where these files are referenced.
    Addressing build error caused by https://github.com/jadonk/beagleconnect/issues/49.
2021-01-22 From Fiona
2021-01-26 mikrobus: add mikrobus submodule and update build-firmware.sh
2021-01-30 README: fix excessive capitalization and change click to add-on board
    fixes wrong build directory in sw/build-firmware.sh
    fixes older buildroot version in README
    Fixes: https://github.com/jadonk/beagleconnect/pull/52#discussion_r566166949
    Fixes: https://github.com/jadonk/beagleconnect/pull/52#discussion_r566178242
    Fixes: https://github.com/jadonk/beagleconnect/pull/52#discussion_r566181604
    Fixes: https://github.com/jadonk/beagleconnect/pull/52#discussion_r566169457
2021-03-05 Update zephyr
2021-03-05 sw: update firmware build script with config to turn on PA
    * update mikrobus-greybus submodule with beagleconnect freedom config
    vaishnav@spectre:~/freedom/beagleconnect/sw$ ./test-net.sh
    ping6 -I lowpan0 ff02::1 -c 5
    + ping6 -I lowpan0 ff02::1 -c 5
    ping6: Warning: source address might be selected on device other than: lowpan0
    PING ff02::1(ff02::1) from :: lowpan0: 56 data bytes
2021-03-05 Use SubG on sensortest, for real
2021-03-08 Add flash support for BeagleConnect Freedom
2021-03-11 temporarily disable sensortag due to flash dts label conflict
2021-03-11 sensortest: reduce message size
2021-03-18 Test w/o external antenna
2021-03-21 zephyr: sgp30: remove debug statements
2021-03-23 sensortest: enable hm3301
2021-03-23 sgp30: minor cleanup
2021-03-25 sensortest: use grove module
2021-03-25 BME680 driver interferes with HDC20X0 driver
2021-04-16 Adjust for fusion-rev boards
2021-04-18 sgp30: debugged
2021-04-27 wpanusb: add make install
2021-04-27 usb_uart_bridge: BEEP hack
2021-04-27 Hack for new HDC2010 address
2021-04-28 sensortest-top.py: add seconds since contact
2021-05-10 sgp30: hack in humidity calibration
2021-05-12 disable BSEC for now
2021-06-06 hm3301: recover I2C bus
2021-06-08 Thoughts on enclosure
2021-06-08 disable HDC2010
2021-06-13 sw: mikrobus: add mikrobus click ID flasher as submodule
    this project allows to flash the eeprom on the new mikrobus click ID adapter from BeagleConnect Freedom,
    the scheme for writing manifests is as follows:
    write production manifest(fixed, minimum information for enabling through userspace if driver is available) at addr 0x0000 onwards
    write variable manifest at next free block after writing production manifest
    update eeprom bytes with production manfiest start block
    write product fixed/production manifest(currently commented)
2021-09-01 ci: add buildroot build for pocketbeagle
    For now, trying to do them in series. Likely need to make parallel builds.
2021-09-02 ci: update buildroot build directories
2021-09-02 buildroot: update qemu kernel version
2021-09-06 buildroot: pocketbeagle: fix postimage script path
2021-09-15 buildroot: switch to SystemD and add ModemManager
2021-10-05 buildroot: update based on recent experiments
    * Use newer u-boot
    * Don't use u-boot patches
    * Increase image size
    * Doesn't have USB boot features I was previously hacking
2021-10-06 msp430: update programming utils
2021-10-06 zephyr/sensortest: debugging rev C4
2021-10-12 buildroot: fix config
2021-10-17 buildroot: WIP
2021-10-18 ads1115: hacking
2021-11-02 CI: add flash python script
2021-11-02 linux: add bcfserial
2021-11-04 Update .gitmodules
    Point to jadonk branches
2021-11-05 greybus-for-zephyr-mikrobus: merge commit for latest
2021-11-05 CI: yet another way to capture tag
2021-11-10 zephyr: hacked in sensor I2C switch
2021-11-11 usb_uart_bridge: change MSP430 I2C address
2021-11-14 for testing latest kernel on C5
2021-11-15 Update to version C5
2021-11-19 sw: flash-msp430.sh: use msp430-env per new readme
2021-12-02 SubG communication workong on rev C5 boards
2021-12-03 Fix wpanusb_bc build issue
2021-12-03 sensortest: add telnet
2021-12-09 Update README.asciidoc
    Stop/Start lowpan.service between cc2538-bsl.py updates
2021-12-09 Fix greybus app commit
2021-12-12 sw: enable greybus app in FW release directory
2022-01-06 Docs: WIP
2022-01-08 usb_uart_bridge: Give CC1352 control over UART mux
2022-01-08 Docs: LED: format as HTML table
2022-01-08 Docs: LED: add some implementation notes
2022-01-11 Add presentation slides
2022-02-11 Gateway enclosure concept
2022-02-18 zephyrproject: Dockerfile remove cmake backport
    this is pulled from our repo now..
2022-02-21 sw: zephyr: Dockerfile: path fix
2022-02-21 sw: zephyr: new sdk
2022-02-26 Update Green_Gateway.md
    Adding Content for Flashing and WiFi usage on the BBGG
2022-03-04 Fixed Forest Mims link
2022-03-04 Final changes for day
2022-04-06 Throw in old test that needs cleanup
2022-04-20 BeagleConnect Freedom C5 back SVG
    This is a Sclable Vector Graphics (Back side) image of the BCF C5 PCB with hand drawn SMD parts using Inkscape.
2022-04-20 BeagleConnect Freedom C5 Back render
    This is a Back side image of the BCF C5 PCB with hand drawn SMD parts using Inkscape.
2022-04-26 BCF in hand image
    BCF Rev C5 in hand image for size perspective.
2022-04-26 Test: Readme PDF output
    Created using AsciidocFX program
2022-04-27 BCF C5 renders
    BCF C5 board back and front render in one image. Individual SVG images for the same are also provided n the graphics folder.
2022-04-27 Update Readme
    New images are added, Instucions are updated and new instuctions are added.
2022-05-01 System Reference Manual Asciidoc file
    This file includes all the section of the SRM for BeagleConnect™, the final SRM is rendered with this file.
2022-05-01 Chapter 2
    This chapter talks about the usage of BeagleConnect™
2022-05-01 Chapter 4
    In this chapter we take a look at greybus stack for BeagleConnect™
2022-05-01 Preface
    This page provides introduction to the thoughts behind creating BeagleConnect™
2022-05-01 SRM
    This is the rendered System Reference Manual (SRM) for BeagleConnect™ which still requires a lots of edits and improvements.
2022-05-03 Install VSCode Server
    Instructions are added to install bb-code-server on BeagleBone green gateway to easily access the terminal and edit code.
2022-05-05 Update LED.md
    WIP
2022-05-06 BCF Block diagram
    New BCF block diagram has been added for Rev C5.
2022-05-06 BeagleConnect back side pinout
    Annotated image shows pinout for beagleconnect back side.
2022-05-06 BeagleConnect new image
    Updated the back image.
2022-05-10 Update block diagram
